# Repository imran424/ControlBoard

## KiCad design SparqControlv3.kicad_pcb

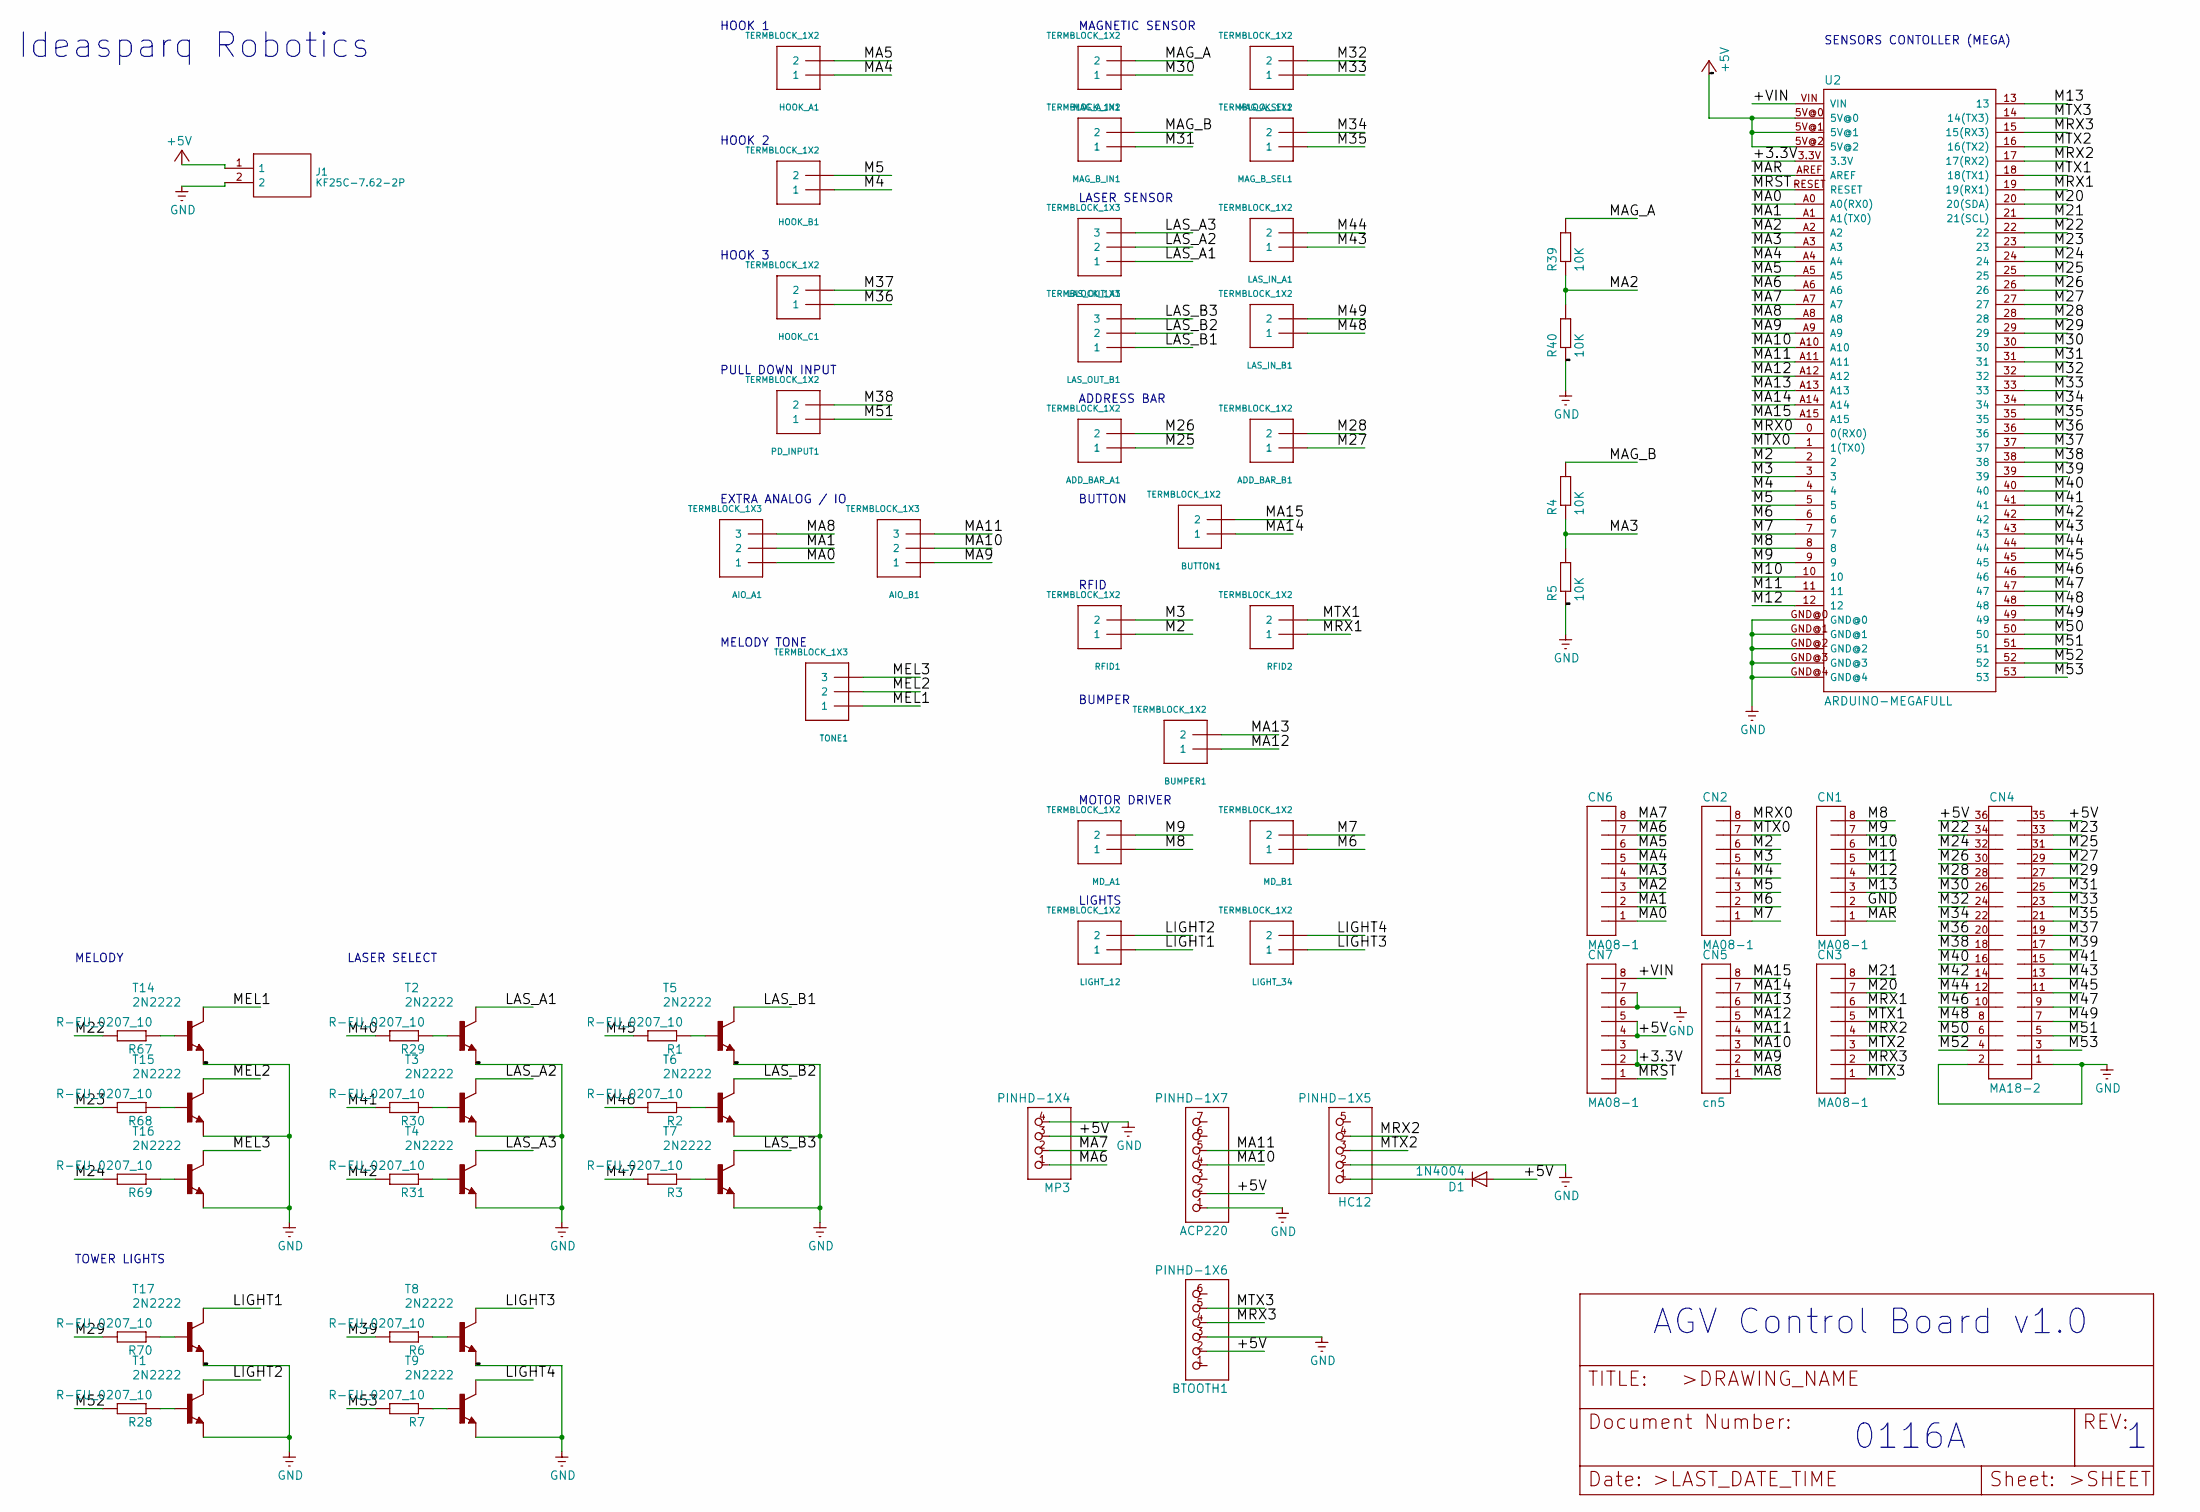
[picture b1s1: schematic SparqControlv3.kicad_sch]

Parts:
ACP220: PINHD-1X7; 1X07
ADD_BAR_A1: TERMBLOCK_1X2; TERMBLOCK_1X2-3.5MM
ADD_BAR_B1: TERMBLOCK_1X2; TERMBLOCK_1X2-3.5MM
AIO_A1: TERMBLOCK_1X3; TERMBLOCK_1X3-3.5MM
AIO_B1: TERMBLOCK_1X3; TERMBLOCK_1X3-3.5MM
BTOOTH1: PINHD-1X6; 1X06
BUMPER1: TERMBLOCK_1X2; TERMBLOCK_1X2-3.5MM
BUTTON1: TERMBLOCK_1X2; TERMBLOCK_1X2-3.5MM
CN1, CN2, CN3, CN6, CN7: MA08-1
CN4: MA18-2
CN5: cn5; MA08-1
D1: 1N4004; DO41-10
HC12: PINHD-1X5; 1X05
HOOK_A1: TERMBLOCK_1X2; TERMBLOCK_1X2-3.5MM
HOOK_B1: TERMBLOCK_1X2; TERMBLOCK_1X2-3.5MM
HOOK_C1: TERMBLOCK_1X2; TERMBLOCK_1X2-3.5MM
J1: KF25C-7.62-2P; KF25C7622P; Manufacturer_Part_Number KF25C-7.62-2P
LAS_IN_A1: TERMBLOCK_1X2; TERMBLOCK_1X2-3.5MM
LAS_IN_B1: TERMBLOCK_1X2; TERMBLOCK_1X2-3.5MM
LAS_OUT_A1: TERMBLOCK_1X3; TERMBLOCK_1X3-3.5MM
LAS_OUT_B1: TERMBLOCK_1X3; TERMBLOCK_1X3-3.5MM
LIGHT_12, LIGHT_34: TERMBLOCK_1X2; TERMBLOCK_1X2-3.5MM
MAG_A_IN1: TERMBLOCK_1X2; TERMBLOCK_1X2-3.5MM
MAG_A_SEL1: TERMBLOCK_1X2; TERMBLOCK_1X2-3.5MM
MAG_B_IN1: TERMBLOCK_1X2; TERMBLOCK_1X2-3.5MM
MAG_B_SEL1: TERMBLOCK_1X2; TERMBLOCK_1X2-3.5MM
MD_A1: TERMBLOCK_1X2; TERMBLOCK_1X2-3.5MM
MD_B1: TERMBLOCK_1X2; TERMBLOCK_1X2-3.5MM
MP3: PINHD-1X4; 1X04
PD_INPUT1: TERMBLOCK_1X2; TERMBLOCK_1X2-3.5MM
R1, R2, R3, R6, R7, R28, R29, R30, R31, R67, R68, R69, R70: R-EU_0207_10; 0207_10
R4, R5, R39, R40: 10K; 0204_7
RFID1, RFID2: TERMBLOCK_1X2; TERMBLOCK_1X2-3.5MM
T1, T2, T3, T4, T5, T6, T7, T8, T9, T14, T15, T16, T17: 2N2222; TO92-EBC-OVAL
TONE1: TERMBLOCK_1X3; TERMBLOCK_1X3-3.5MM
U2: ARDUINO-MEGAFULL; ARDUINO_MEGA

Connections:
+5V: ACP220.2, BTOOTH1.2, CN4.35, CN4.36, CN7.4, CN7.5, D1.A, J1.1, MP3.3, U2.5V@0, U2.5V@1, U2.5V@2
/+3.3V: CN7.2, CN7.3, U2.3.3V
/+VIN: CN7.8, U2.VIN
/LAS_A1: LAS_OUT_A1.1, T2.C
/LAS_A2: LAS_OUT_A1.2, T3.C
/LAS_A3: LAS_OUT_A1.3, T4.C
/LAS_B1: LAS_OUT_B1.1, T5.C
/LAS_B2: LAS_OUT_B1.2, T6.C
/LAS_B3: LAS_OUT_B1.3, T7.C
/LIGHT1: LIGHT_12.1, T17.C
/LIGHT2: LIGHT_12.2, T1.C
/LIGHT3: LIGHT_34.1, T8.C
/LIGHT4: LIGHT_34.2, T9.C
/M2: CN2.6, RFID1.1, U2.2
/M3: CN2.5, RFID1.2, U2.3
/M4: CN2.4, HOOK_B1.1, U2.4
/M5: CN2.3, HOOK_B1.2, U2.5
/M6: CN2.2, MD_B1.1, U2.6
/M7: CN2.1, MD_B1.2, U2.7
/M8: CN1.8, MD_A1.1, U2.8
/M9: CN1.7, MD_A1.2, U2.9
/M10: CN1.6, U2.10
/M11: CN1.5, U2.11
/M12: CN1.4, U2.12
/M13: CN1.3, U2.13
/M20: CN3.7, U2.20 (20(SDA))
/M21: CN3.8, U2.21 (21(SCL))
/M22: CN4.34, R67.2, U2.22
/M23: CN4.33, R68.2, U2.23
/M24: CN4.32, R69.2, U2.24
/M25: ADD_BAR_A1.1, CN4.31, U2.25
/M26: ADD_BAR_A1.2, CN4.30, U2.26
/M27: ADD_BAR_B1.1, CN4.29, U2.27
/M28: ADD_BAR_B1.2, CN4.28, U2.28
/M29: CN4.27, R70.2, U2.29
/M30: CN4.26, MAG_A_IN1.1, U2.30
/M31: CN4.25, MAG_B_IN1.1, U2.31
/M32: CN4.24, MAG_A_SEL1.2, U2.32
/M33: CN4.23, MAG_A_SEL1.1, U2.33
/M34: CN4.22, MAG_B_SEL1.2, U2.34
/M35: CN4.21, MAG_B_SEL1.1, U2.35
/M36: CN4.20, HOOK_C1.1, U2.36
/M37: CN4.19, HOOK_C1.2, U2.37
/M38: CN4.18, PD_INPUT1.2, U2.38
/M39: CN4.17, R6.2, U2.39
/M40: CN4.16, R29.2, U2.40
/M41: CN4.15, R30.2, U2.41
/M42: CN4.14, R31.2, U2.42
/M43: CN4.13, LAS_IN_A1.1, U2.43
/M44: CN4.12, LAS_IN_A1.2, U2.44
/M45: CN4.11, R1.2, U2.45
/M46: CN4.10, R2.2, U2.46
/M47: CN4.9, R3.2, U2.47
/M48: CN4.8, LAS_IN_B1.1, U2.48
/M49: CN4.7, LAS_IN_B1.2, U2.49
/M50: CN4.6, U2.50
/M51: CN4.5, PD_INPUT1.1, U2.51
/M52: CN4.4, R28.2, U2.52
/M53: CN4.3, R7.2, U2.53
/MA0: AIO_A1.1, CN6.1, U2.A0 (A0(RX0))
/MA1: AIO_A1.2, CN6.2, U2.A1 (A1(TX0))
/MA2: CN6.3, R39.2, R40.1, U2.A2
/MA3: CN6.4, R4.2, R5.1, U2.A3
/MA4: CN6.5, HOOK_A1.1, U2.A4
/MA5: CN6.6, HOOK_A1.2, U2.A5
/MA6: CN6.7, MP3.1, U2.A6
/MA7: CN6.8, MP3.2, U2.A7
/MA8: AIO_A1.3, CN5.1, U2.A8
/MA9: AIO_B1.1, CN5.2, U2.A9
/MA10: ACP220.4, AIO_B1.2, CN5.3, U2.A10
/MA11: ACP220.5, AIO_B1.3, CN5.4, U2.A11
/MA12: BUMPER1.1, CN5.5, U2.A12
/MA13: BUMPER1.2, CN5.6, U2.A13
/MA14: BUTTON1.1, CN5.7, U2.A14
/MA15: BUTTON1.2, CN5.8, U2.A15
/MAG_A: MAG_A_IN1.2, R39.1
/MAG_B: MAG_B_IN1.2, R4.1
/MAR: CN1.1, U2.AREF
/MEL1: T14.C, TONE1.1
/MEL2: T15.C, TONE1.2
/MEL3: T16.C, TONE1.3
/MRST: CN7.1, U2.RESET
/MRX0: CN2.8, U2.0 (0(RX0))
/MRX1: CN3.6, RFID2.1, U2.19 (19(RX1))
/MRX2: CN3.4, HC12.4, U2.17 (17(RX2))
/MRX3: BTOOTH1.4, CN3.2, U2.15 (15(RX3))
/MTX0: CN2.7, U2.1 (1(TX0))
/MTX1: CN3.5, RFID2.2, U2.18 (18(TX1))
/MTX2: CN3.3, HC12.3, U2.16 (16(TX2))
/MTX3: BTOOTH1.5, CN3.1, U2.14 (14(TX3))
GND: ACP220.1, BTOOTH1.3, CN1.2, CN4.1, CN4.2, CN7.6, CN7.7, HC12.2, J1.2, MP3.4, R5.2, R40.2, T1.E, T2.E, T3.E, T4.E, T5.E, T6.E, T7.E, T8.E, T9.E, T14.E, T15.E, T16.E, T17.E, U2.GND@0, U2.GND@1, U2.GND@2, U2.GND@3, U2.GND@4
unnamed: D1.C, HC12.1
unnamed: R1.1, T5.B
unnamed: R2.1, T6.B
unnamed: R3.1, T7.B
unnamed: R6.1, T8.B
unnamed: R7.1, T9.B
unnamed: R28.1, T1.B
unnamed: R29.1, T2.B
unnamed: R30.1, T3.B
unnamed: R31.1, T4.B
unnamed: R67.1, T14.B
unnamed: R68.1, T15.B
unnamed: R69.1, T16.B
unnamed: R70.1, T17.B

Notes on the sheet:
BUTTON
BUMPER
HOOK 3
LASER SENSOR
0116A
MELODY
EXTRA ANALOG / IO
HOOK 1
SENSORS CONTOLLER (MEGA)
LIGHTS
MELODY TONE
AGV Control Board v1.0
MOTOR DRIVER
PULL DOWN INPUT
TOWER LIGHTS
Ideasparq Robotics
MAGNETIC SENSOR
LASER SELECT
HOOK 2
RFID
ADDRESS BAR

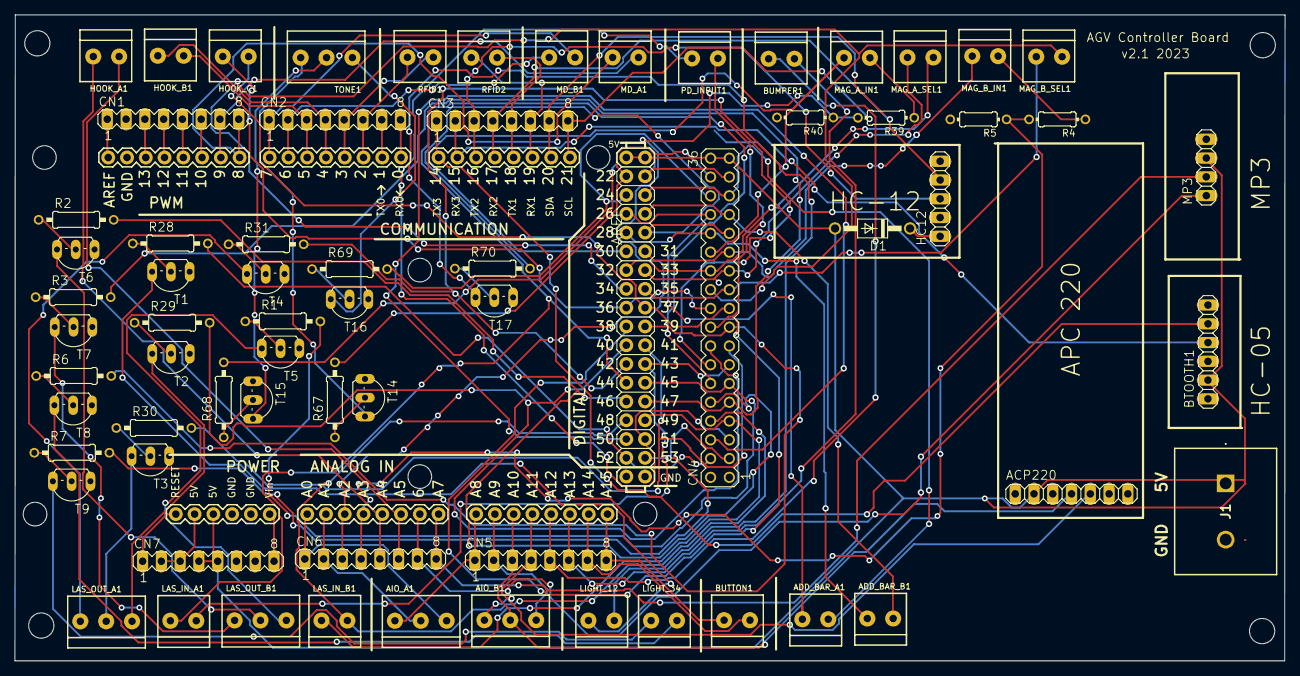
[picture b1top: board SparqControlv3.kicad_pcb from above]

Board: 2 copper layers, 171.8 x 87.3 mm, 69 parts (0 on the bottom side), 105 nets.

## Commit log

2025-04-18 init commit
2025-04-18 Reapply "init commit"
    This reverts commit bcfbd88f921e8642ab9e486e1b4637bfb609005a.
2025-04-18 Revert "init commit"
    This reverts commit 523d6443049e11406ff04419274ca574d6d6cd16.
